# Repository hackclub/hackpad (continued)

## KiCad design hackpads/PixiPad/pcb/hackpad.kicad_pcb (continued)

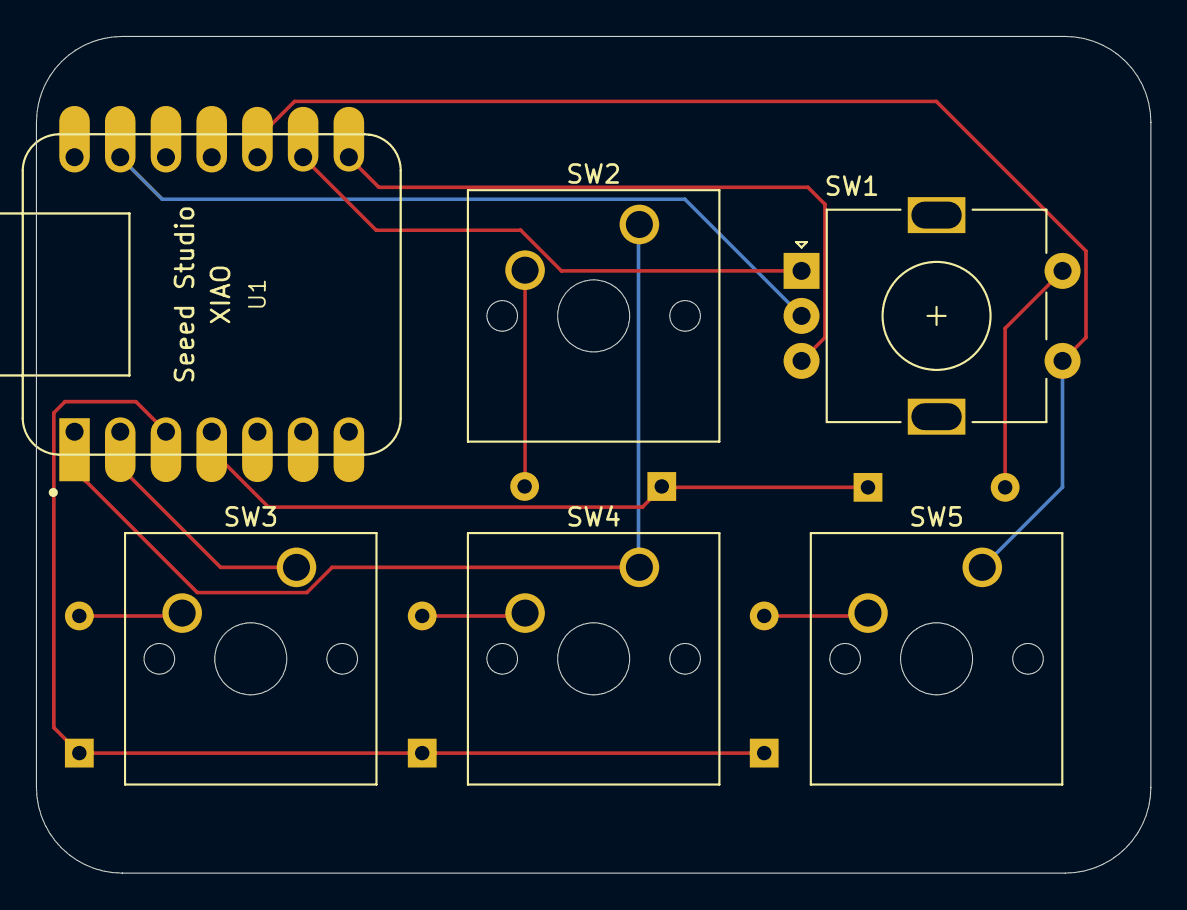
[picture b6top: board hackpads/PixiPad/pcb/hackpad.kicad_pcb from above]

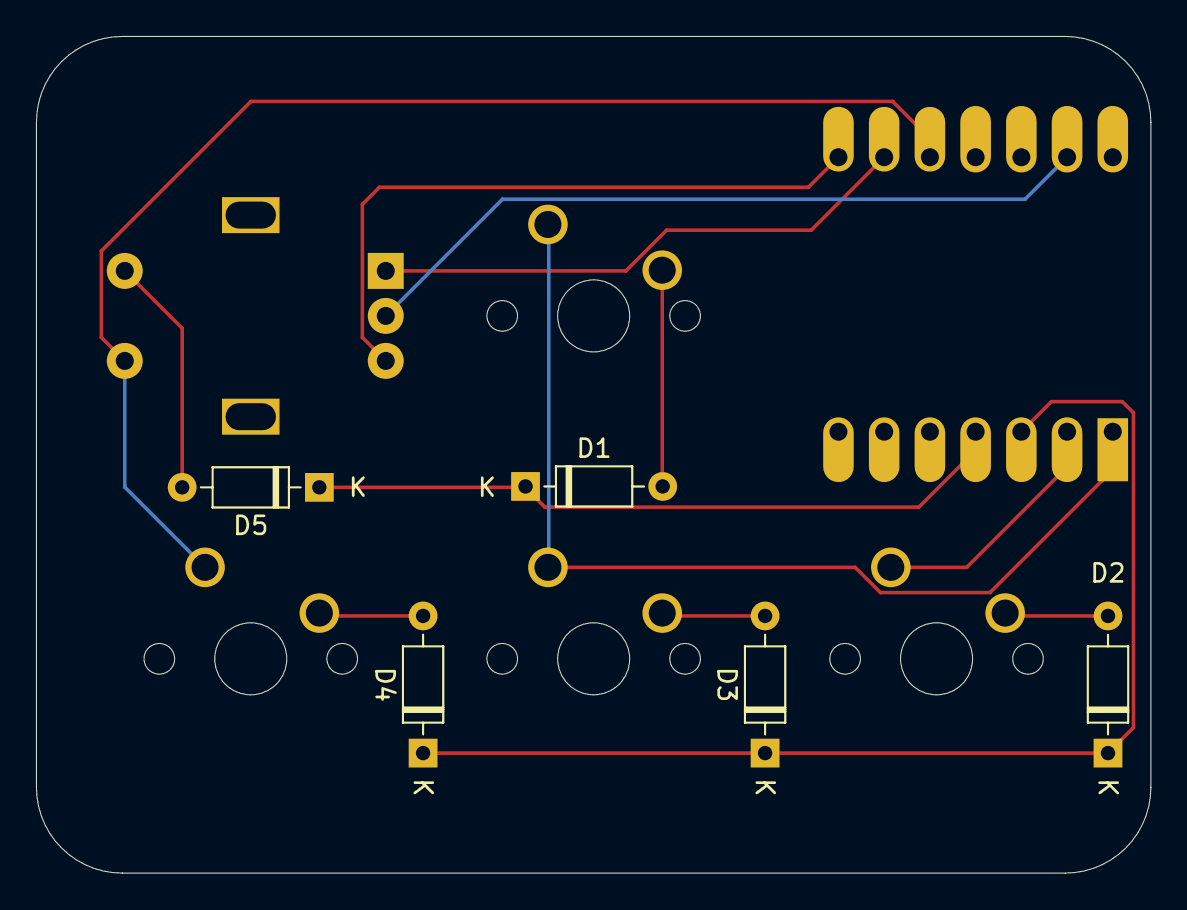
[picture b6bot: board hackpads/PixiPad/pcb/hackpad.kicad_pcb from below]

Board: 2 copper layers, 61.9 x 46.5 mm, 11 parts (5 on the bottom side), 13 nets.

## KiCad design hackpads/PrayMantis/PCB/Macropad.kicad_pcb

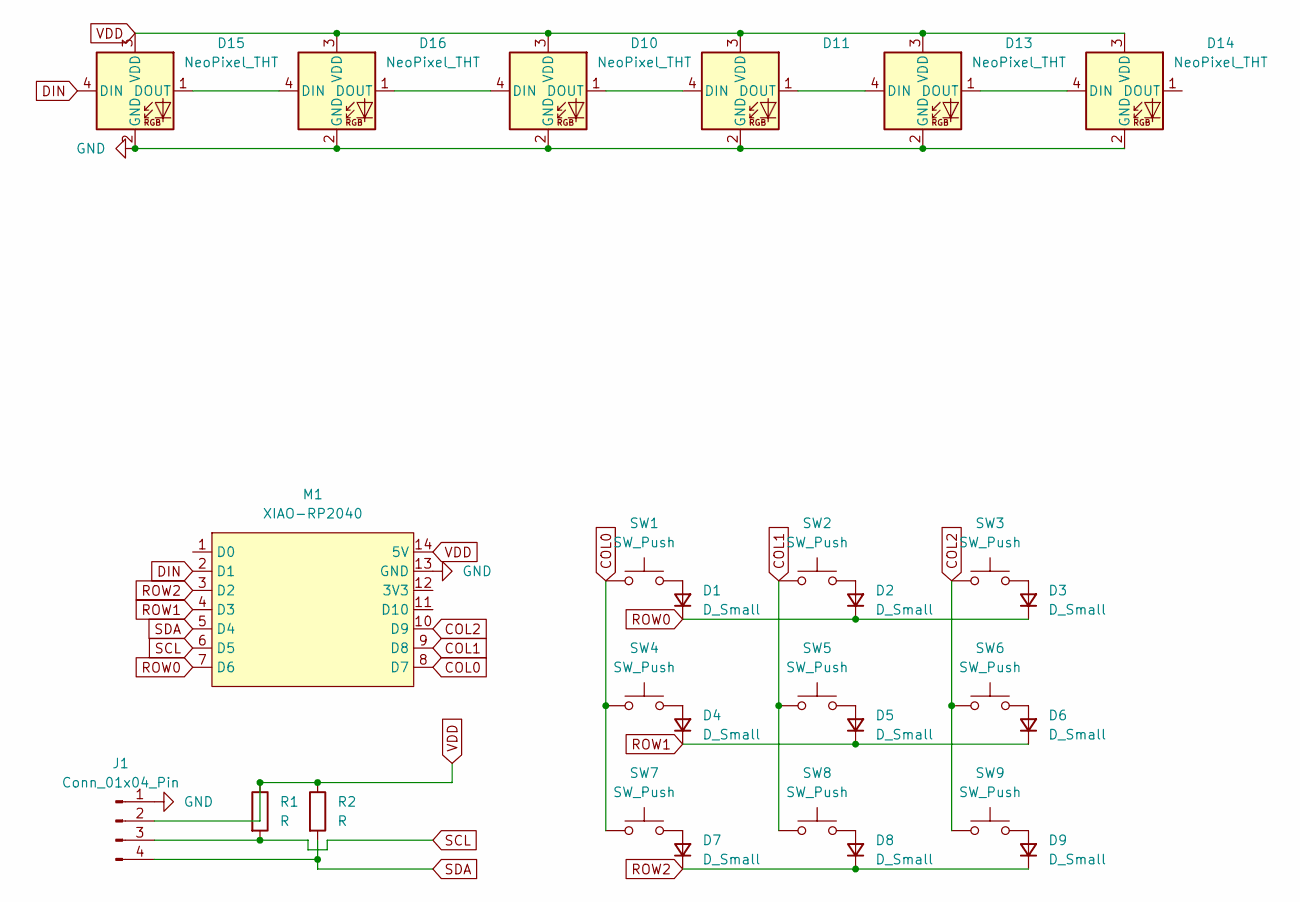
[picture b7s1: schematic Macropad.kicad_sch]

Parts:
D1, D2, D3, D4, D5, D6, D7, D8, D9: D_Small; DIODE-1N4148
D10, D11, D13, D14, D15, D16: NeoPixel_THT; LED_OPSCO_SK6812_PLCC4_5.0x5.0mm_P3.1mm
J1: Conn_01x04_Pin; screen
M1: XIAO-RP2040; xiao
R1, R2: R; R_Axial_DIN0207_L6.3mm_D2.5mm_P10.16mm_Horizontal
SW1, SW2, SW3, SW4, SW5, SW6, SW7, SW8, SW9: SW_Push; SW_Cherry_MX_1.00u_PCB

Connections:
COL0: M1.8 (D7), SW1.1, SW4.1, SW7.1
COL1: M1.9 (D8), SW2.1, SW5.1, SW8.1
COL2: M1.10 (D9), SW3.1, SW6.1, SW9.1
DIN: D15.4 (DIN), M1.2 (D1)
GND: D10.2 (GND), D11.2 (GND), D13.2 (GND), D14.2 (GND), D15.2 (GND), D16.2 (GND), J1.1, M1.13 (GND)
unnamed: D1.A, SW1.2
unnamed: D2.A, SW2.2
unnamed: D3.A, SW3.2
unnamed: D4.A, SW4.2
unnamed: D5.A, SW5.2
unnamed: D6.A, SW6.2
unnamed: D7.A, SW7.2
unnamed: D8.A, SW8.2
unnamed: D9.A, SW9.2
unnamed: D10.4 (DIN), D16.1 (DOUT)
unnamed: D10.1 (DOUT), D11.4 (DIN)
unnamed: D11.1 (DOUT), D13.4 (DIN)
unnamed: D13.1 (DOUT), D14.4 (DIN)
unnamed: D15.1 (DOUT), D16.4 (DIN)
ROW0: D1.K, D2.K, D3.K, M1.7 (D6)
ROW1: D4.K, D5.K, D6.K, M1.4 (D3)
ROW2: D7.K, D8.K, D9.K, M1.3 (D2)
SCL: J1.3, M1.6 (D5), R1.2
SDA: J1.4, M1.5 (D4), R2.2

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
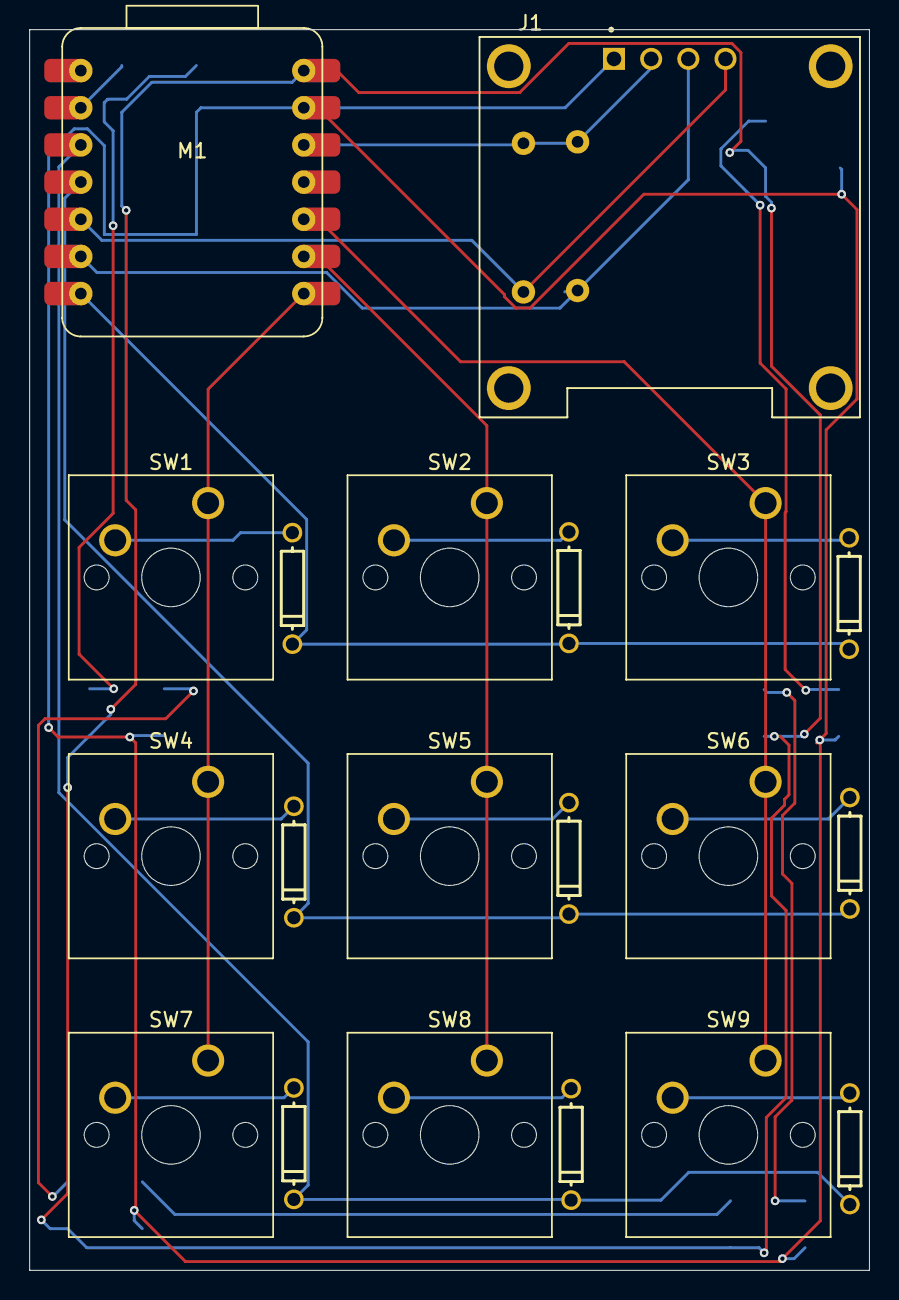
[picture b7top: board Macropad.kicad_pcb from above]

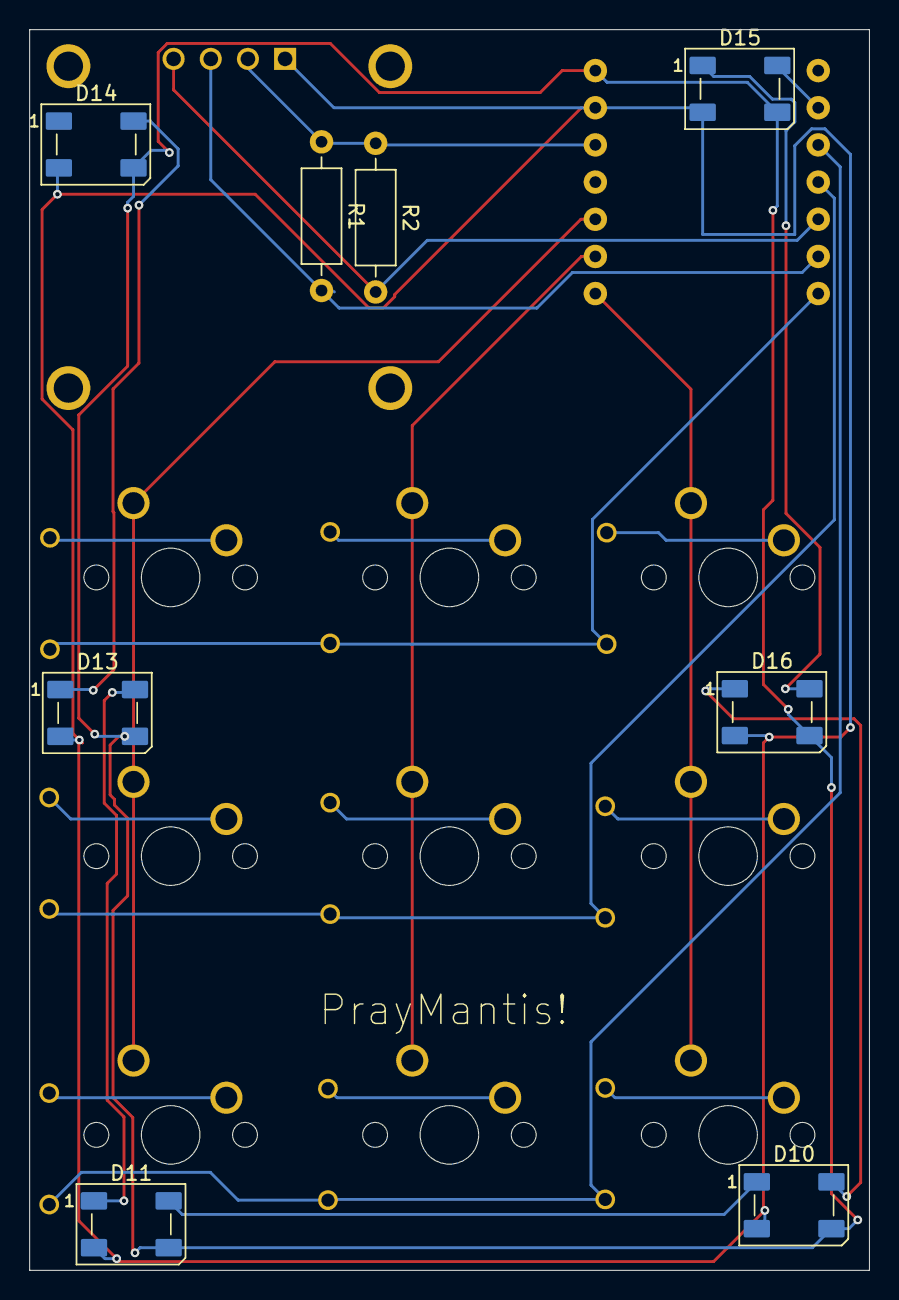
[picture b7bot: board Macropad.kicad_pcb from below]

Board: 2 copper layers, 57.4 x 84.8 mm, 28 parts (8 on the bottom side), 26 nets.
